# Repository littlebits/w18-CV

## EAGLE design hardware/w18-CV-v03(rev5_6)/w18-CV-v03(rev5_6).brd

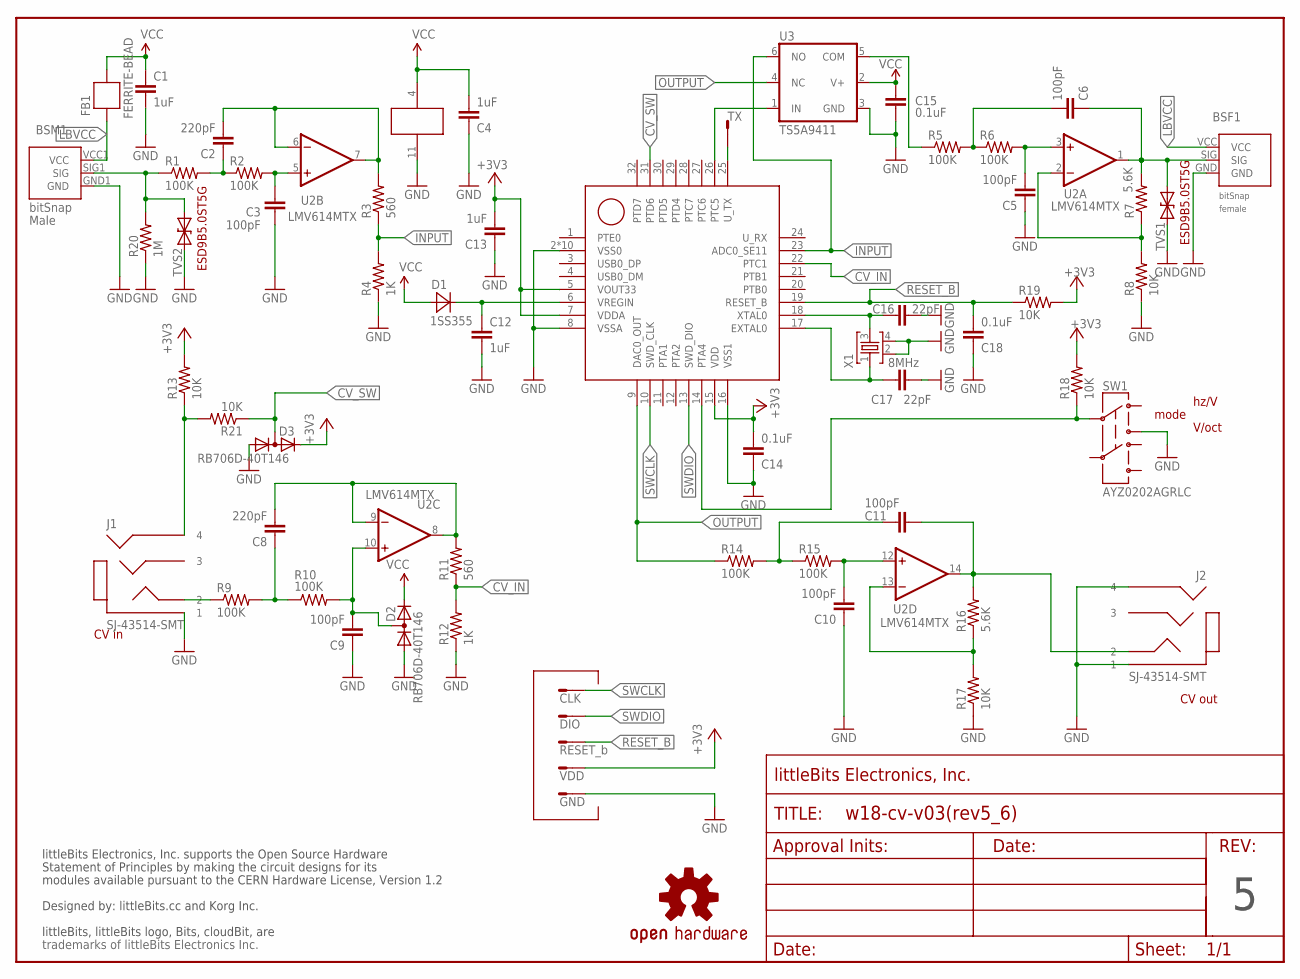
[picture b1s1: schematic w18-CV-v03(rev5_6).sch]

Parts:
BSF1: BITSNAP_V03_FEMALE
BSM1: BITSNAP_V03_MALE
C1, C4, C12, C13: 1uF; CC_1608_0.8_TBR_LB_1PRIMARY
C2, C8: 220pF; CC_1608_0.8_TBR_LB_1PRIMARY
C3, C5, C6, C9, C10, C11: 100pF; CC_1608_0.8_TBR_LB_1PRIMARY
C14, C15, C18: 0.1uF; CC_1608_0.8_TBR_LB_1PRIMARY
C16, C17: 22pF; CC_1608_0.8_TBR_LB_1PRIMARY
D1: 1SS355; DISC_ROHM-UMD2_#_TBR_LB_1PRIMARY
D2, D3: RB706D-40T146; SOT23C
FB1: FERRITE-BEAD; R0603
FRAME1: FRAME-LETTER-OHWOHW; FABDWG01-OHW
J1, J2: SJ-43514-SMT; LB_K_CN_SJ-43514-SMT_LB
JP1: GND; TEST_POINT_1PRIMARY
JP2: VDD; TEST_POINT_1PRIMARY
JP3: RESET_b; TEST_POINT_1PRIMARY
JP4: DIO; TEST_POINT_1PRIMARY
JP5: CLK; TEST_POINT_1PRIMARY
JP6: TX; TEST_POINT_1PRIMARY
R1, R2, R5, R6, R9, R10, R14, R15: 100K; R_1608_LB
R3, R11: 560; R_1608_LB
R4, R12: 1K; R_1608_LB
R7, R16: 5.6K; R_1608_LB
R8, R13, R17, R18, R19, R21: 10K; R_1608_LB
R20: 1M; R_1608_LB
SW1: AYZ0202AGRLC; SW_MS-22C01_#_TBR_LB_1PRIMARY
TVS1, TVS2: ESD9B5.0ST5G; SOD-923
U1: MKL26Z64VFM4; IC_TI-QFN32_0.5_TBR_LB_1PRIMARY
U2: LMV614MTX; IC_TSSOP14-225_0.65_TBR_LB_1PRIMARY
U3: TS5A9411; IC_SSOP6-W2.1_0.65_TBR_LB_1PRIMARY
U$1: OSHWCREDIT-KORG
U$5: OSHW-LOGOL; OSHW-LOGO-L
X1: 8MHz; X_ROSON_RT5_#_TBR_LB_1PRIMARY

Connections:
+3V3: C13.2, C14.2, D3.2 (K), JP2.1, R13.2, R18.2, R19.2, U1.5 (VOUT33), U1.7 (VDDA), U1.15 (VDD)
CV_IN: R11.1, R12.2, U1.22 (PTC1)
CV_SW: D3.3 (AK), R21.1, U1.31 (PTD6)
GND: BSF1.GND, BSM1.GND1 (GND), C1.2, C3.1, C4.1, C5.1, C9.1, C10.1, C12.2, C13.1, C14.1, C15.1, C16.1, C17.1, C18.1, D2.1 (A), D3.1 (A), J1.1, J2.1, J2.4, JP1.1, R4.1, R8.1, R12.1, R17.1, R20.1, SW1.3, TVS1.1 (A), TVS2.1 (A), U1.2 (VSS0), U1.8 (VSSA), U1.16 (VSS1), U1.33 (VSS0), U1.34 (VSS0), U1.35 (VSS0), U1.36 (VSS0), U1.37 (VSS0), U1.38 (VSS0), U1.39 (VSS0), U1.40 (VSS0), U1.41 (VSS0), U2.11 (V-), U3.3 (GND), X1.2, X1.4
INPUT: R3.1, R4.2, U1.23 (ADC0_SE11), U3.6 (NO)
JCK_DET: J1.4, R13.1, R21.2
LBVCC: BSF1.VCC, BSM1.VCC1 (VCC), FB1.2
unnamed: BSM1.SIG1 (SIG), R1.1, R20.2, TVS2.2 (C)
unnamed: C2.2, R3.2, U2.6 (-IN), U2.7 (OUT)
unnamed: C3.2, R2.2, U2.5 (+IN)
unnamed: C2.1, R1.2, R2.1
unnamed: R5.1, U3.5 (COM)
unnamed: BSF1.SIG, C6.1, R7.2, TVS1.2 (C), U2.1 (OUT)
unnamed: J1.2, R9.1
unnamed: C12.1, D1.2, U1.6 (VREGIN)
unnamed: C6.2, R5.2, R6.1
unnamed: C5.2, R6.2, U2.3 (+IN)
unnamed: R18.1, SW1.2, U1.14 (PTA4)
unnamed: C9.2, D2.3 (AK), R10.2, U2.10 (+IN)
unnamed: C8.1, R9.2, R10.1
unnamed: U1.26 (PTC5), U3.1 (IN)
unnamed: C17.2, U1.17 (EXTAL0), X1.1
unnamed: C16.2, U1.18 (XTAL0), X1.3
unnamed: C11.2, R14.2, R15.1
unnamed: C10.2, R15.2, U2.12 (+IN)
unnamed: R7.1, R8.2, U2.2 (-IN)
unnamed: C11.1, J2.2, R16.2, U2.14 (OUT)
unnamed: R16.1, R17.2, U2.13 (-IN)
NETR: C8.2, R11.2, U2.8 (OUT), U2.9 (-IN)
OUTPUT: R14.1, U1.9 (DAC0_OUT), U3.4 (NC)
RESET_B: C18.2, JP3.1, R19.1, U1.19 (RESET_B)
SWCLK: JP5.1, U1.10 (SWD_CLK)
SWDIO: JP4.1, U1.13 (SWD_DIO)
TX: JP6.1, U1.25 (U_TX)
VCC: C1.1, C4.2, C15.2, D1.1, D2.2 (K), FB1.1, U2.4 (V+), U3.2 (V+)

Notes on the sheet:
V/oct
hz/V
mode
CV in
CV out

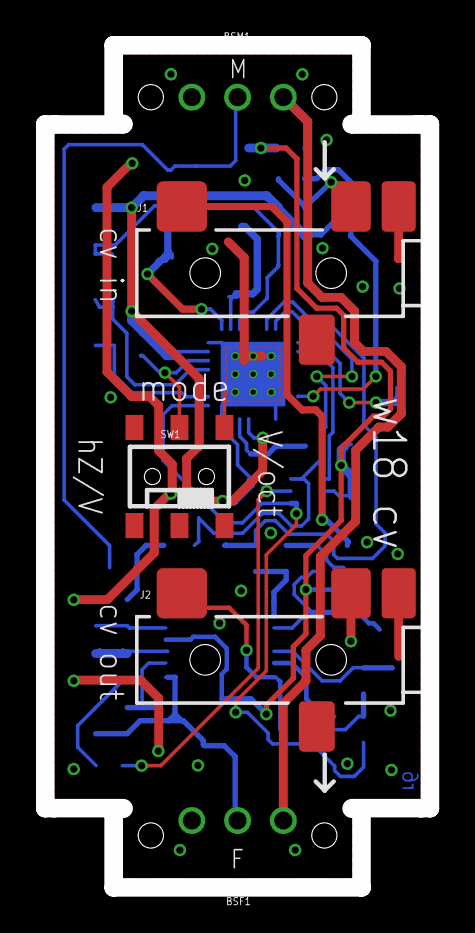
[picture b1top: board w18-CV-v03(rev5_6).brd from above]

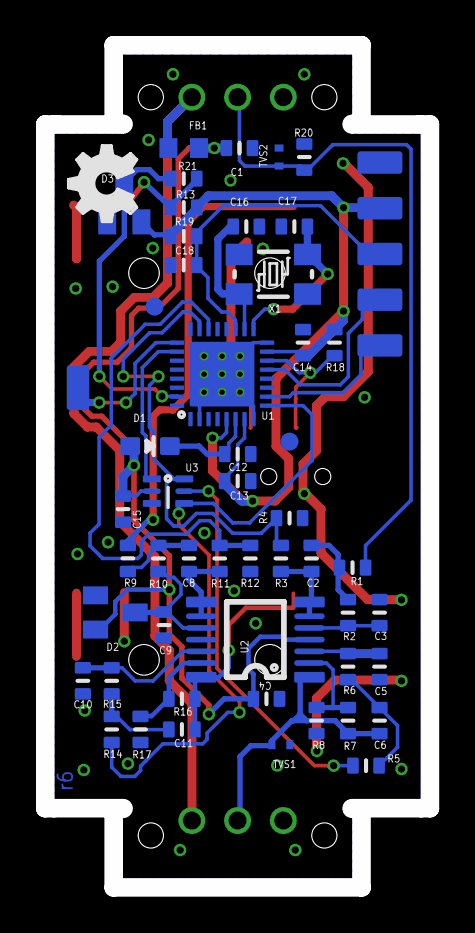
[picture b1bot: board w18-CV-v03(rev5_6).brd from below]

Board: 2 copper layers, 21.4 x 46.8 mm, 63 parts (55 on the bottom side), 35 nets.

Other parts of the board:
E$30: OSHW_FILLX150_NOTEXT

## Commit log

2015-04-21 First commit, added hardware files

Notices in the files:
parts and their libraries:
LITTLEBITS: modules available pursuant to the CERN Hardware License, Version 1.2
